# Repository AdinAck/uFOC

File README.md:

# uFOC
 A high density FOC BLDC motor controller utilizing GaN FETs for maximum performance while maintaining a miniature footprint.

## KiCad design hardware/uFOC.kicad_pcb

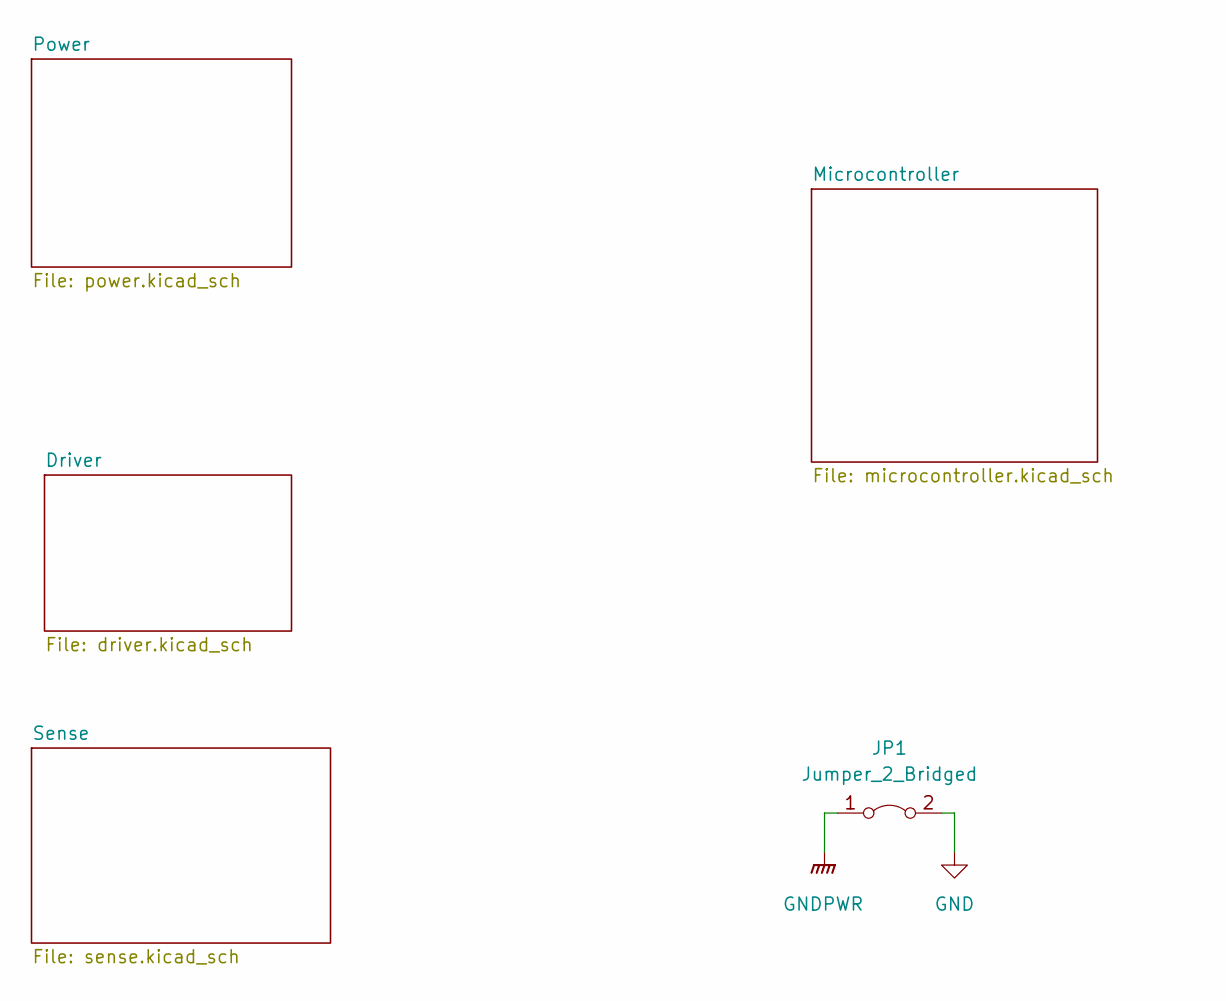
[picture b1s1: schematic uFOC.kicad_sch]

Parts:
JP1: Jumper_2_Bridged

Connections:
GND: JP1.2 (B); also elsewhere on the board
GNDPWR: JP1.1 (A); also elsewhere on the board

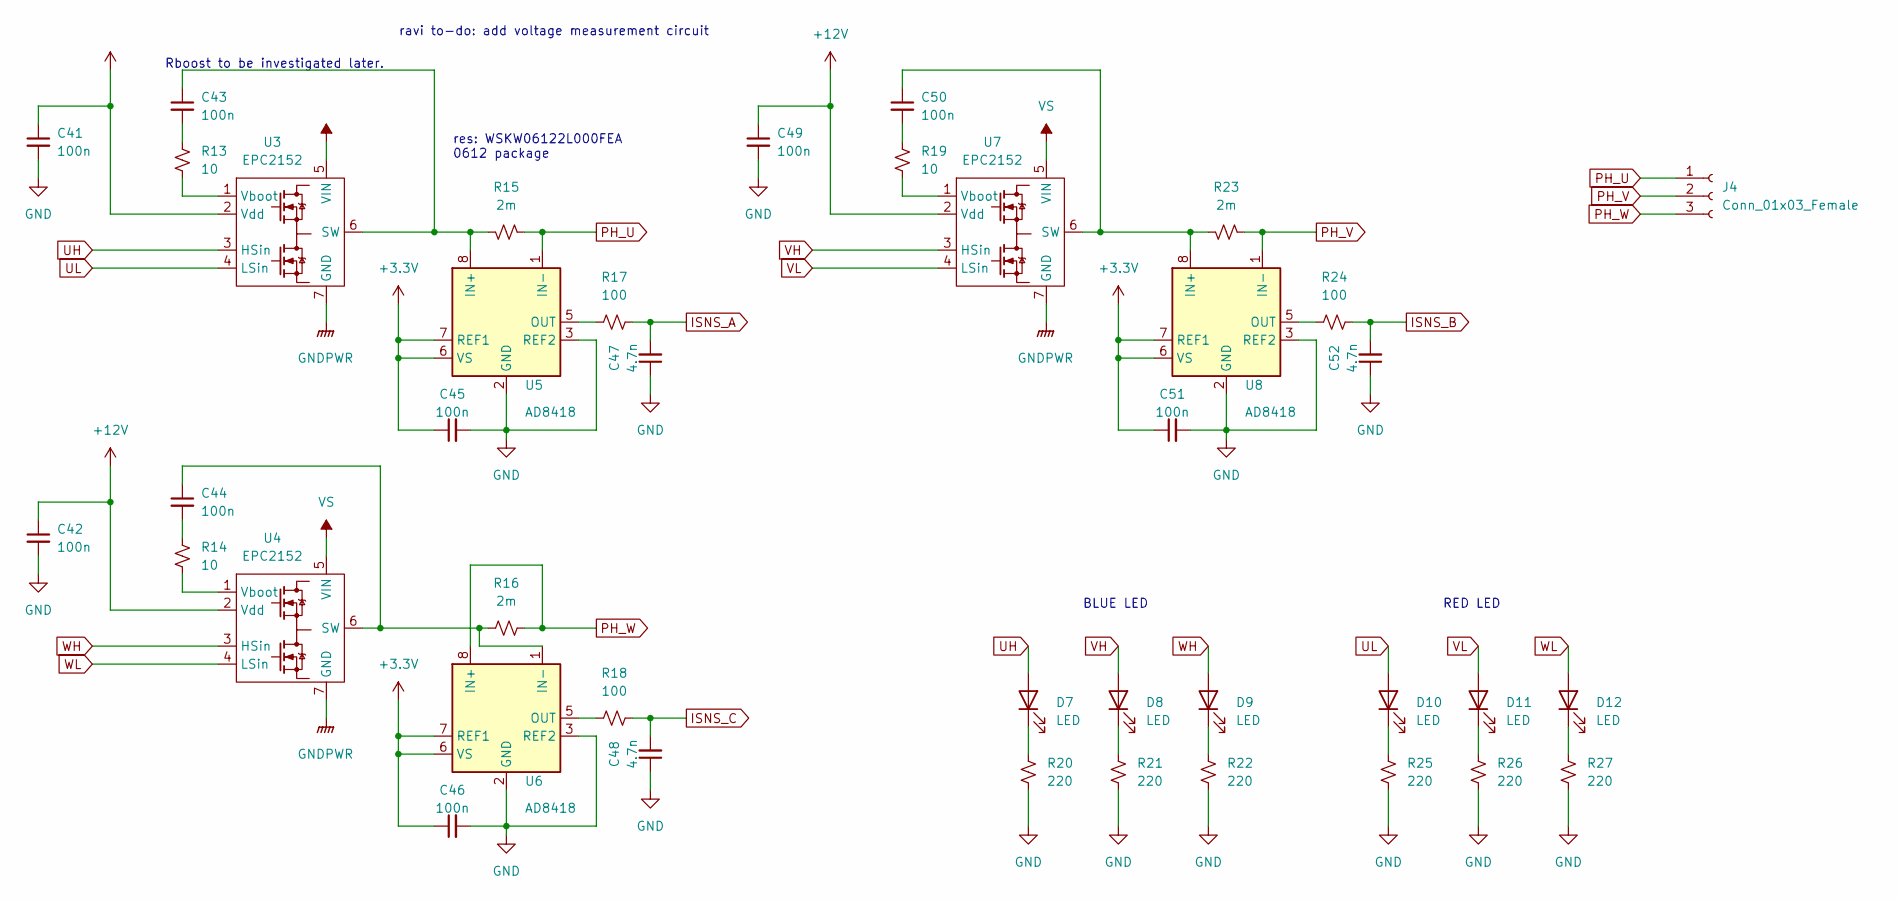
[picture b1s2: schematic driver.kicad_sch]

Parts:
C41, C42, C43, C44, C45, C46, C49, C50, C51: 100n; C_0805_2012Metric_Pad1.18x1.45mm_HandSolder
C47, C48, C52: 4.7n; C_0805_2012Metric_Pad1.18x1.45mm_HandSolder
D7, D8, D9, D10, D11, D12: LED; LED_0805_2012Metric
J4: Conn_01x03_Female; 1716090000
R13, R14, R19: 10; C_0805_2012Metric_Pad1.18x1.45mm_HandSolder
R15, R16, R23: 2m; WSKW06122L000FEA
R17, R18, R24: 100; R_0805_2012Metric
R20, R21, R22, R25, R26, R27: 220; R_0805_2012Metric
U3, U4, U7: EPC2152
U5, U6, U8: AD8418; MSOP-8-1EP_3x3mm_P0.65mm_EP1.68x1.88mm

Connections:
GND: C41.2, C42.2, C45.2, C46.2, C47.1, C48.1, C49.2, C51.2, C52.1, R20.2, R21.2, R22.2, R25.2, R26.2, R27.2, U5.2 (GND), U5.3 (REF2), U6.2 (GND), U6.3 (REF2), U8.2 (GND), U8.3 (REF2); also elsewhere on the board
GNDPWR: U3.7 (GND), U4.7 (GND), U7.7 (GND); also elsewhere on the board
ISNS_A: C47.2, R17.2; also elsewhere on the board
ISNS_B: C52.2, R24.2; also elsewhere on the board
ISNS_C: C48.2, R18.2; also elsewhere on the board
unnamed: C43.1, R15.2, U3.6 (SW), U5.8 (IN+)
unnamed: C43.2, R13.1
unnamed: C44.1, R16.1, U4.6 (SW), U6.1 (IN-)
unnamed: C44.2, R14.1
unnamed: C50.1, R23.2, U7.6 (SW), U8.8 (IN+)
unnamed: C50.2, R19.1
unnamed: D7.1 (K), R20.1
unnamed: D8.1 (K), R21.1
unnamed: D9.1 (K), R22.1
unnamed: D10.1 (K), R25.1
unnamed: D11.1 (K), R26.1
unnamed: D12.1 (K), R27.1
unnamed: R13.2, U3.1 (Vboot)
unnamed: R14.2, U4.1 (Vboot)
unnamed: R17.1, U5.5 (OUT)
unnamed: R18.1, U6.5 (OUT)
unnamed: R19.2, U7.1 (Vboot)
unnamed: R24.1, U8.5 (OUT)
PH_U: J4.1, R15.1, U5.1 (IN-)
PH_V: J4.2, R23.1, U8.1 (IN-)
PH_W: J4.3, R16.2, U6.8 (IN+); also elsewhere on the board
UH: D7.2 (A), U3.3 (HSin); also elsewhere on the board
UL: D10.2 (A), U3.4 (LSin); also elsewhere on the board
VH: D8.2 (A), U7.3 (HSin); also elsewhere on the board
VL: D11.2 (A), U7.4 (LSin); also elsewhere on the board
WH: D9.2 (A), U4.3 (HSin); also elsewhere on the board
WL: D12.2 (A), U4.4 (LSin); also elsewhere on the board

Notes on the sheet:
res: WSKW06122L000FEA 0612 package
BLUE LED
ravi to-do: add voltage measurement circuit
Rboost to be investigated later.
RED LED

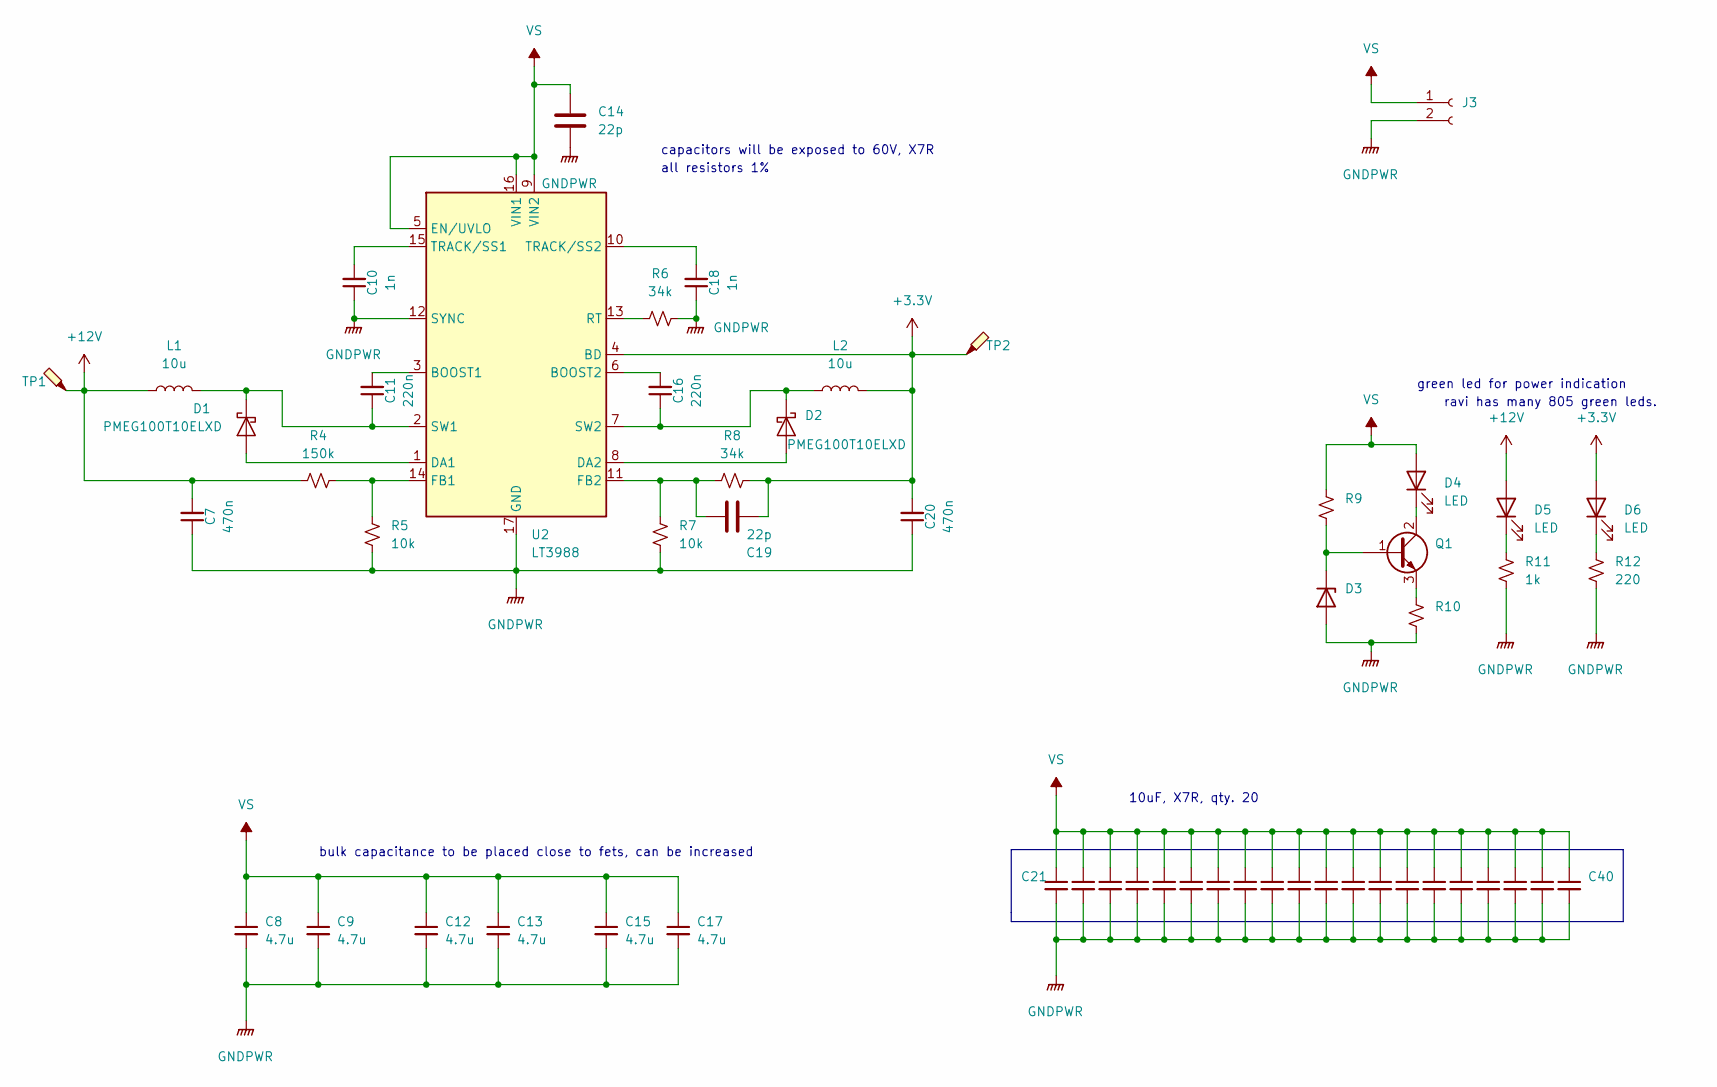
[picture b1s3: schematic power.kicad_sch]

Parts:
C7, C20: 470n; C_0805_2012Metric_Pad1.18x1.45mm_HandSolder
C8, C9, C12, C13, C15, C17: 4.7u; C_1206_3216Metric_Pad1.33x1.80mm_HandSolder
C10, C18: 1n; C_0805_2012Metric_Pad1.18x1.45mm_HandSolder
C11, C16: 220n; C_0805_2012Metric_Pad1.18x1.45mm_HandSolder
C14, C19: 22p; C_0402_1005Metric_Pad0.74x0.62mm_HandSolder
C21, C22, C40: C_1210_3225Metric
C23, C24, C25, C26, C27, C28, C29, C30, C31, C32, C33, C34, C35, C36, C37, C38, C39: 10u; C_1210_3225Metric
D1, D2: PMEG100T10ELXD; D_SOD-323F
D3: D_SOD-523
D4, D5, D6: LED; LED_0805_2012Metric
J3: (no value)
L1, L2: 10u; L_Taiyo-Yuden_MD-3030
Q1: SOT-89-3
R4: 150k; C_0805_2012Metric_Pad1.18x1.45mm_HandSolder
R5, R7: 10k; R_0805_2012Metric
R6, R8: 34k; R_0805_2012Metric
R9, R10: R_0805_2012Metric
R11: 1k; R_0805_2012Metric
R12: 220; R_0805_2012Metric
TP1: (no value)
TP2: TestPoint_Probe
U2: LT3988; MSOP-16-1EP_3x4mm_P0.5mm_EP1.65x2.85mm

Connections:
GNDPWR: C7.1, C8.2, C9.2, C10.1, C12.2, C13.2, C14.1, C15.2, C17.2, C18.1, C20.1, C21.2, C22.2, C23.2, C24.2, C25.2, C26.2, C27.2, C28.2, C29.2, C30.2, C31.2, C32.2, C33.2, C34.2, C35.2, C36.2, C37.2, C38.2, C39.2, C40.2, D3.2 (A), J3.2, R5.2, R6.1, R7.2, R10.2, R11.2, R12.2, U2.12 (SYNC), U2.17 (GND); also elsewhere on the board
unnamed: C10.2, U2.15 (TRACK/SS1)
unnamed: C11.1, D1.1 (K), L1.2, U2.2 (SW1)
unnamed: C11.2, U2.3 (BOOST1)
unnamed: C16.1, D2.1 (K), L2.1, U2.7 (SW2)
unnamed: C16.2, U2.6 (BOOST2)
unnamed: C18.2, U2.10 (TRACK/SS2)
unnamed: C19.2, R7.1, R8.2, U2.11 (FB2)
unnamed: D1.2 (A), U2.1 (DA1)
unnamed: D2.2 (A), U2.8 (DA2)
unnamed: D3.1 (K), Q1.1 (B), R9.2
unnamed: D4.1 (K), Q1.2 (C)
unnamed: D5.1 (K), R11.1
unnamed: D6.1 (K), R12.1
unnamed: Q1.3 (E), R10.1
unnamed: R4.1, R5.1, U2.14 (FB1)
unnamed: R6.2, U2.13 (RT)

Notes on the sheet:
all resistors 1%
10uF, X7R, qty. 20
green led for power indication
capacitors will be exposed to 60V, X7R
ravi has many 805 green leds.
bulk capacitance to be placed close to fets, can be increased

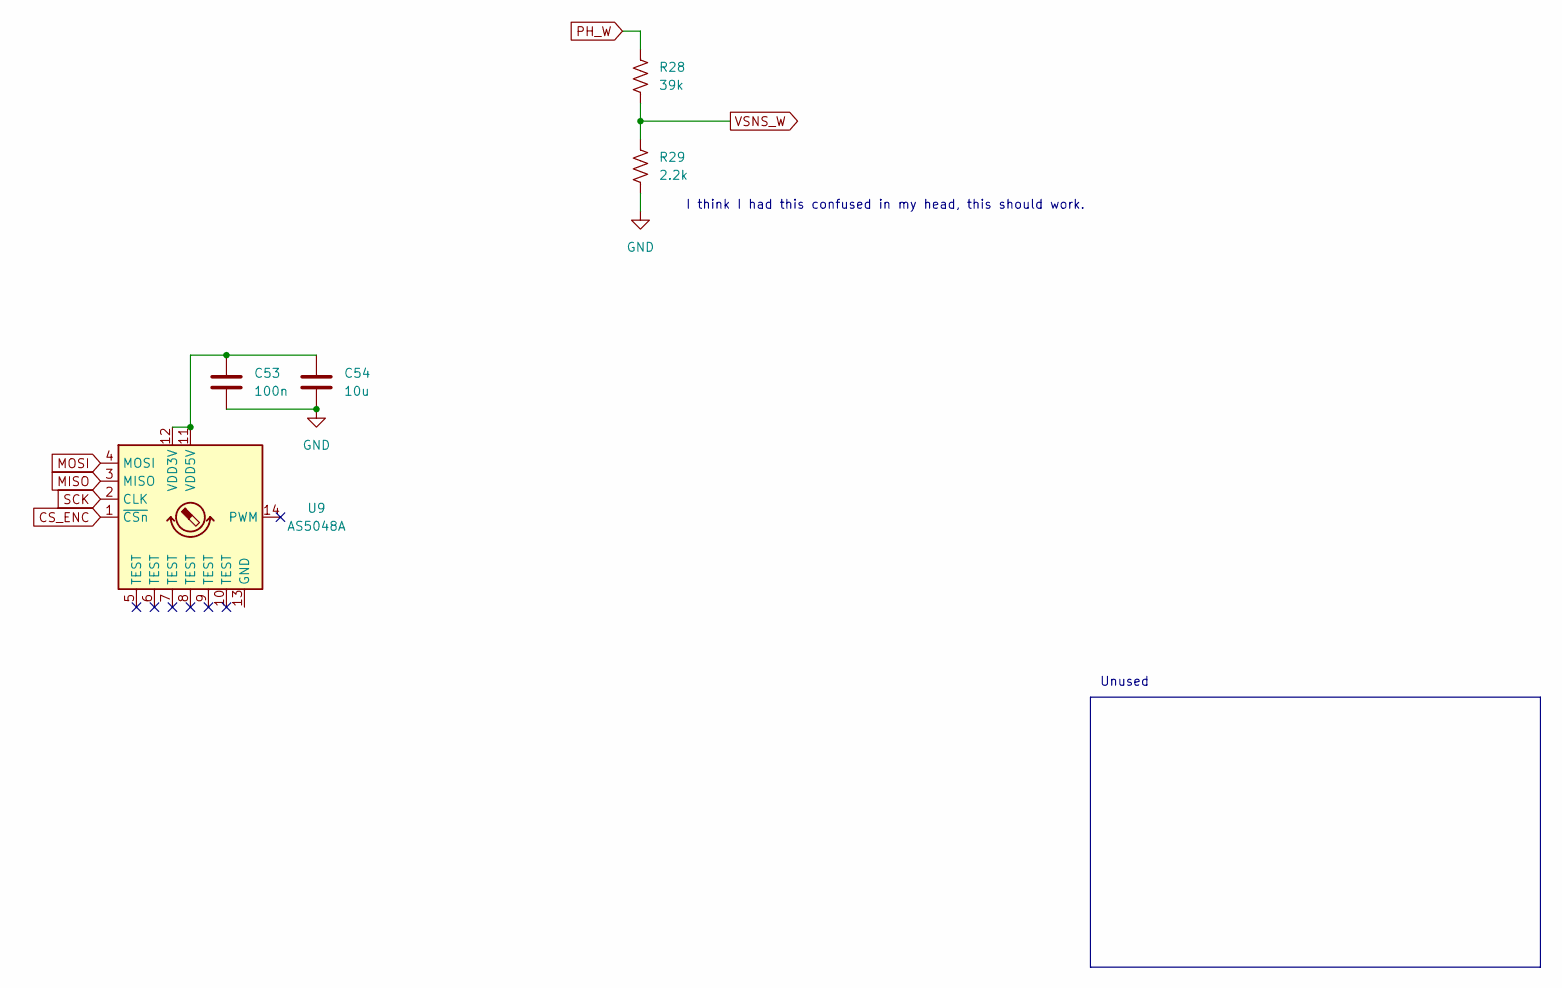
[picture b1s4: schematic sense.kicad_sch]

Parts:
C53: 100n; C_0402_1005Metric
C54: 10u; C_0805_2012Metric
R28: 39k; R_0805_2012Metric
R29: 2.2k; R_0805_2012Metric
U9: AS5048A; TSSOP-14_4.4x5mm_P0.65mm

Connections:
CS_ENC: U9.1 (~CSn)
GND: C53.2, C54.2, R29.1; also elsewhere on the board
MISO: U9.3 (MISO); also elsewhere on the board
MOSI: U9.4 (MOSI); also elsewhere on the board
unnamed: C53.1, C54.1, U9.11 (VDD5V), U9.12 (VDD3V)
PH_W: R28.2; also elsewhere on the board
SCK: U9.2 (CLK); also elsewhere on the board
VSNS_W: R28.1, R29.2

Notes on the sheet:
Unused
I think I had this confused in my head, this should work.

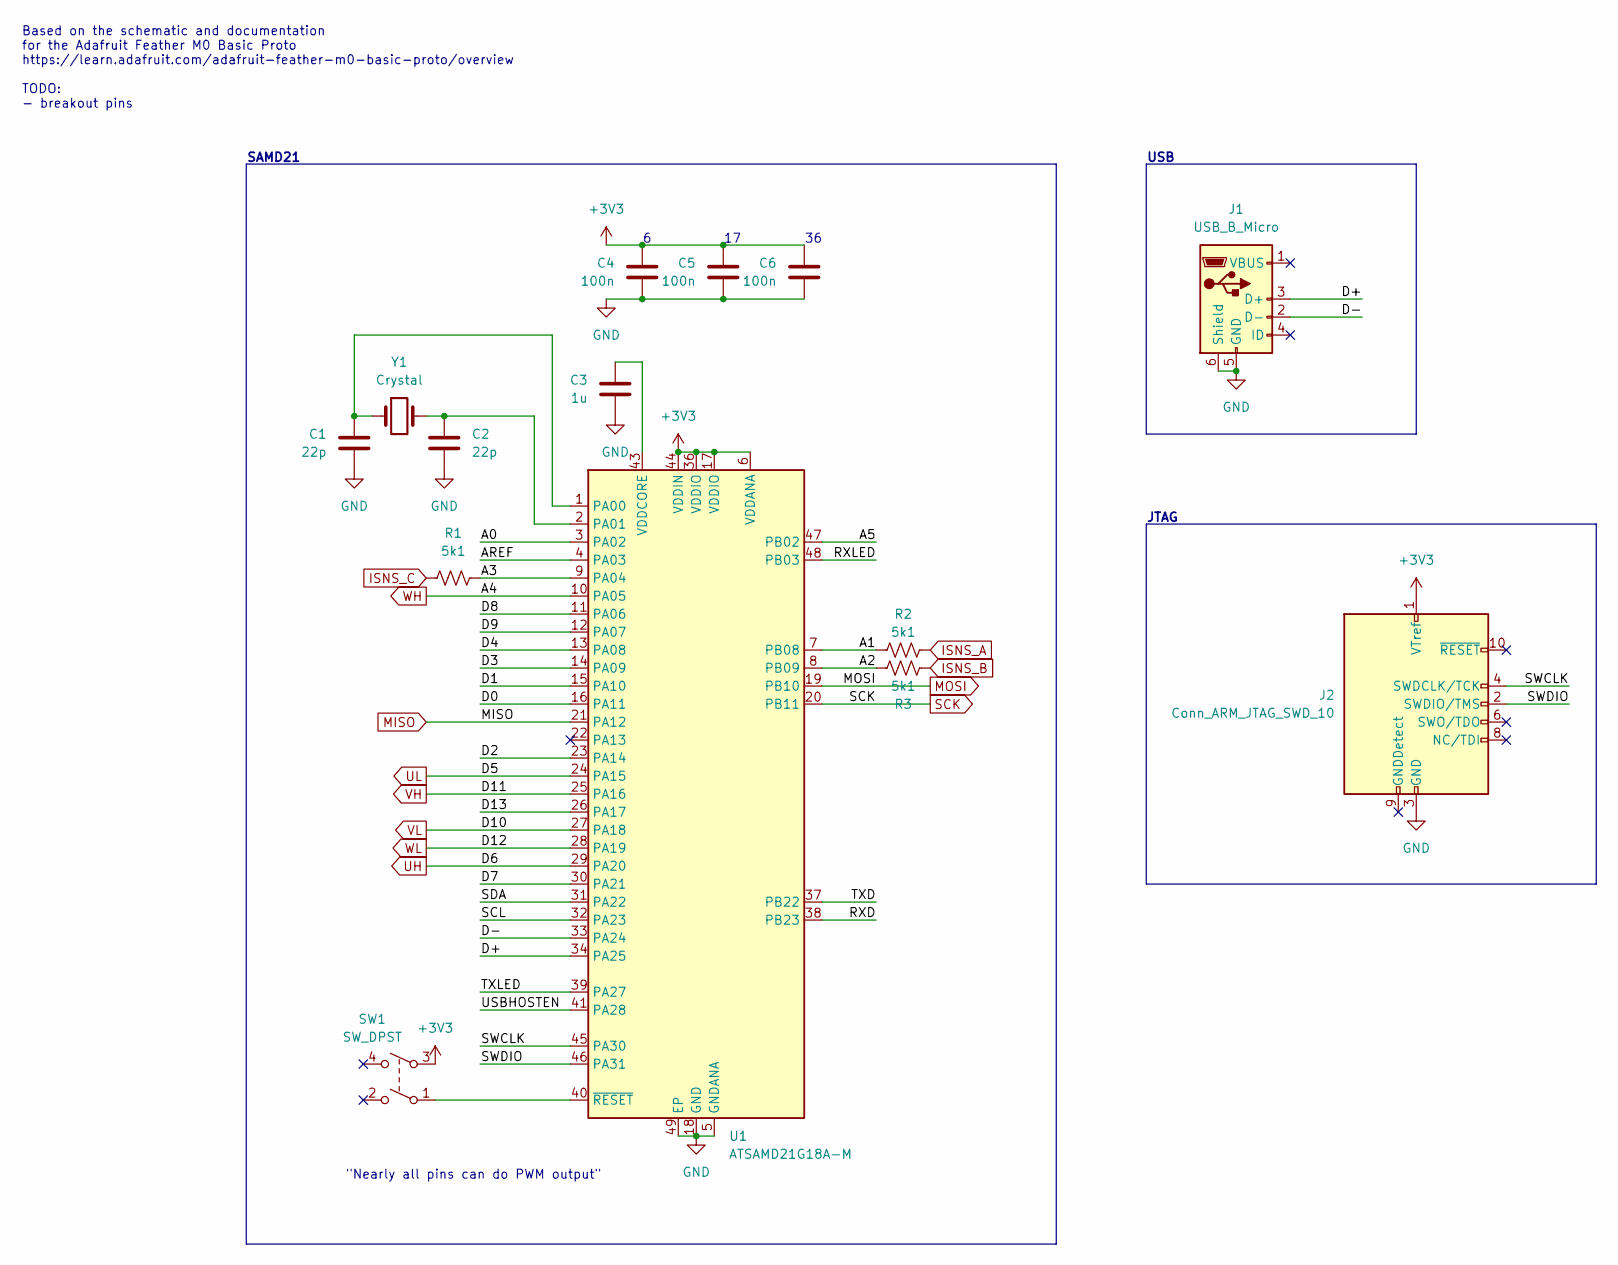
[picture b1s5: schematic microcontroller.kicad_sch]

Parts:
C1, C2: 22p; C_0805_2012Metric
C3: 1u; C_0805_2012Metric
C4, C5, C6: 100n; C_0805_2012Metric
J1: USB_B_Micro; USB_Micro-B_Molex_47346-0001
J2: Conn_ARM_JTAG_SWD_10; PinHeader_2x05_P1.27mm_Vertical_SMD
R1, R2, R3: 5k1; R_0805_2012Metric
SW1: SW_DPST; EVQ-P2402M
U1: ATSAMD21G18A-M; QFN-48-1EP_7x7mm_P0.5mm_EP5.15x5.15mm
Y1: Crystal; Crystal_SMD_MicroCrystal_CC8V-T1A-2Pin_2.0x1.2mm

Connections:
/Microcontroller/A0: U1.3 (PA02)
/Microcontroller/A1: R2.1, U1.7 (PB08)
/Microcontroller/A2: R3.1, U1.8 (PB09)
/Microcontroller/A3: R1.2, U1.9 (PA04)
/Microcontroller/A5: U1.47 (PB02)
/Microcontroller/AREF: U1.4 (PA03)
/Microcontroller/D0: U1.16 (PA11)
/Microcontroller/D1: U1.15 (PA10)
/Microcontroller/D2: U1.23 (PA14)
/Microcontroller/D3: U1.14 (PA09)
/Microcontroller/D4: U1.13 (PA08)
/Microcontroller/D7: U1.30 (PA21)
/Microcontroller/D8: U1.11 (PA06)
/Microcontroller/D9: U1.12 (PA07)
/Microcontroller/D13: U1.26 (PA17)
/Microcontroller/D+: J1.3 (D+), U1.34 (PA25)
/Microcontroller/D-: J1.2 (D-), U1.33 (PA24)
/Microcontroller/RXD: U1.38 (PB23)
/Microcontroller/RXLED: U1.48 (PB03)
/Microcontroller/SCL: U1.32 (PA23)
/Microcontroller/SDA: U1.31 (PA22)
/Microcontroller/SWCLK: J2.4 (SWDCLK/TCK), U1.45 (PA30)
/Microcontroller/SWDIO: J2.2 (SWDIO/TMS), U1.46 (PA31)
/Microcontroller/TXD: U1.37 (PB22)
/Microcontroller/TXLED: U1.39 (PA27)
/Microcontroller/USBHOSTEN: U1.41 (PA28)
GND: C1.1, C2.2, C3.1, C4.1, C5.1, C6.1, J1.5 (GND), J1.6 (Shield), J2.3 (GND), J2.5 (GND), U1.5 (GNDANA), U1.18 (GND), U1.35 (GND), U1.42 (GND), U1.49 (EP); also elsewhere on the board
ISNS_A: R2.2; also elsewhere on the board
ISNS_B: R3.2; also elsewhere on the board
ISNS_C: R1.1; also elsewhere on the board
MISO: U1.21 (PA12); also elsewhere on the board
MOSI: U1.19 (PB10); also elsewhere on the board
unnamed: C1.2, U1.1 (PA00), Y1.1
unnamed: C2.1, U1.2 (PA01), Y1.2
unnamed: C3.2, U1.43 (VDDCORE)
unnamed: SW1.1, U1.40 (~RESET)
SCK: U1.20 (PB11); also elsewhere on the board
UH: U1.29 (PA20); also elsewhere on the board
UL: U1.24 (PA15); also elsewhere on the board
VH: U1.25 (PA16); also elsewhere on the board
VL: U1.27 (PA18); also elsewhere on the board
WH: U1.10 (PA05); also elsewhere on the board
WL: U1.28 (PA19); also elsewhere on the board

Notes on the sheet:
USB
SAMD21
Based on the schematic and documentation for the Adafruit Feather M0 Basic Proto https://learn.adafruit.com/adafruit-feather-m0-basic-proto/overview TODO: - breakout pins
JTAG
"Nearly all pins can do PWM output"

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
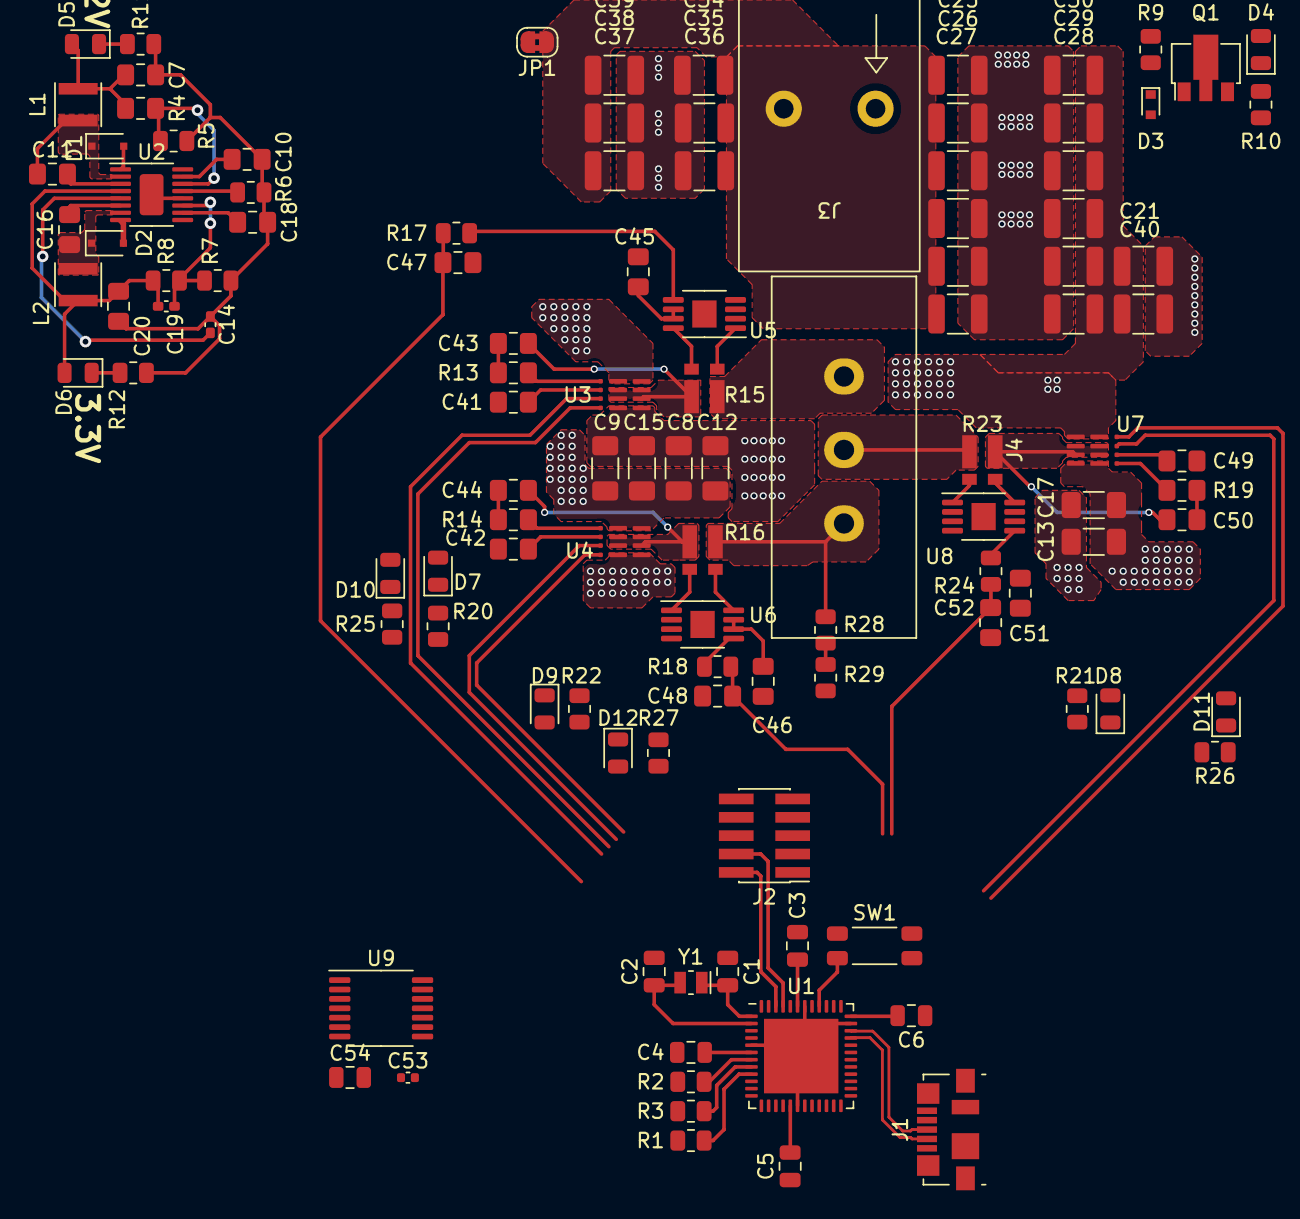
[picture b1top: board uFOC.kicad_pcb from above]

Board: 4 copper layers, 114 parts (0 on the bottom side), 67 nets.

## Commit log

2022-06-20 Version 1 of driver and current sense.
2022-06-21 added buck converter rev1
    still need to pick inductors, size bulk capacitance, verify calcs
2022-06-27 Started Buck Layout
2022-07-02 small changes
2022-07-10 workin away
2022-07-10 microcontroller done?
2022-07-10 sourcing parts
2022-07-10 Net changes, sense changes
2022-07-10 swd interface
2022-07-10 led and other misc
2022-07-11 signal leds, bulk capacitance
2022-07-14 cleanup microcontroller sheet and increase verbosity
2022-07-20 some layout
2022-08-03 Simplified sensing, added some power layout.
